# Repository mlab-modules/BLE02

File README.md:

# BLE02 - Dual-Mode Bluetooth HCI Controller

BLE02 is a dual-mode Bluetooth Low Energy controller module based on the CC2564C HCI compatible chipset.  
The module provides UART (HCI) and PCM/I²S digital audio interface and is designed as a compact MLAB building block for integration with external MCU/MPU systems.

The RF section, clocks and power conditioning are implemented on-board. The host processor should handle the Bluetooth stack via HCI transport.

## Key Features

- Dual-mode Bluetooth controller (BR/EDR + LE, Bluetooth 5.1 compliant)
- HCI transport over UART (up to 4 Mbit/s)
- PCM / I²S digital audio interface
- Class 1 transmitter capability (up to +12 dBm)
- Integrated LDO regulator from 3.3V power source
- 26 MHz main crystal oscillator
- 32.768 kHz low-power clock oscillator
- 1.8 V I/O domain (level shifted to 3.3 V on module connectors)
- Single-ended 50 Ω RF interface on MCX connector

The module uses the chip in HCI mode. All higher Bluetooth layers must run on the host MCU.

## Electrical Parameters

### Supply

- **VCC (module input):** 3.3 V nominal
- On-board regulation:
  - CC2564C powered directly from power input
  - I/O domain: 1.8 V (generated internally, exposed as VDD_1V8)
- Typical consumption:
  - TX (GFSK, max power): ~100 mA
  - LE advertising: 200 µA average
  - Shutdown: less than 10 µA

## UART Interface (HCI)

- Transport: H4 (UART)
- Baud rate: 38.4 kbit/s to 4 Mbit/s
- Hardware flow control required (RTS/CTS)

The controller signals boot completion by asserting RTS low after reset.

## Audio Interface (PCM / I²S)

- PCM master or slave mode
- Up to 4.096 MHz bit clock
- Suitable for HFP, A2DP and other audio profiles

Note: Assisted modes (WBS, A2DP assist) cannot be used simultaneously with LE mode.

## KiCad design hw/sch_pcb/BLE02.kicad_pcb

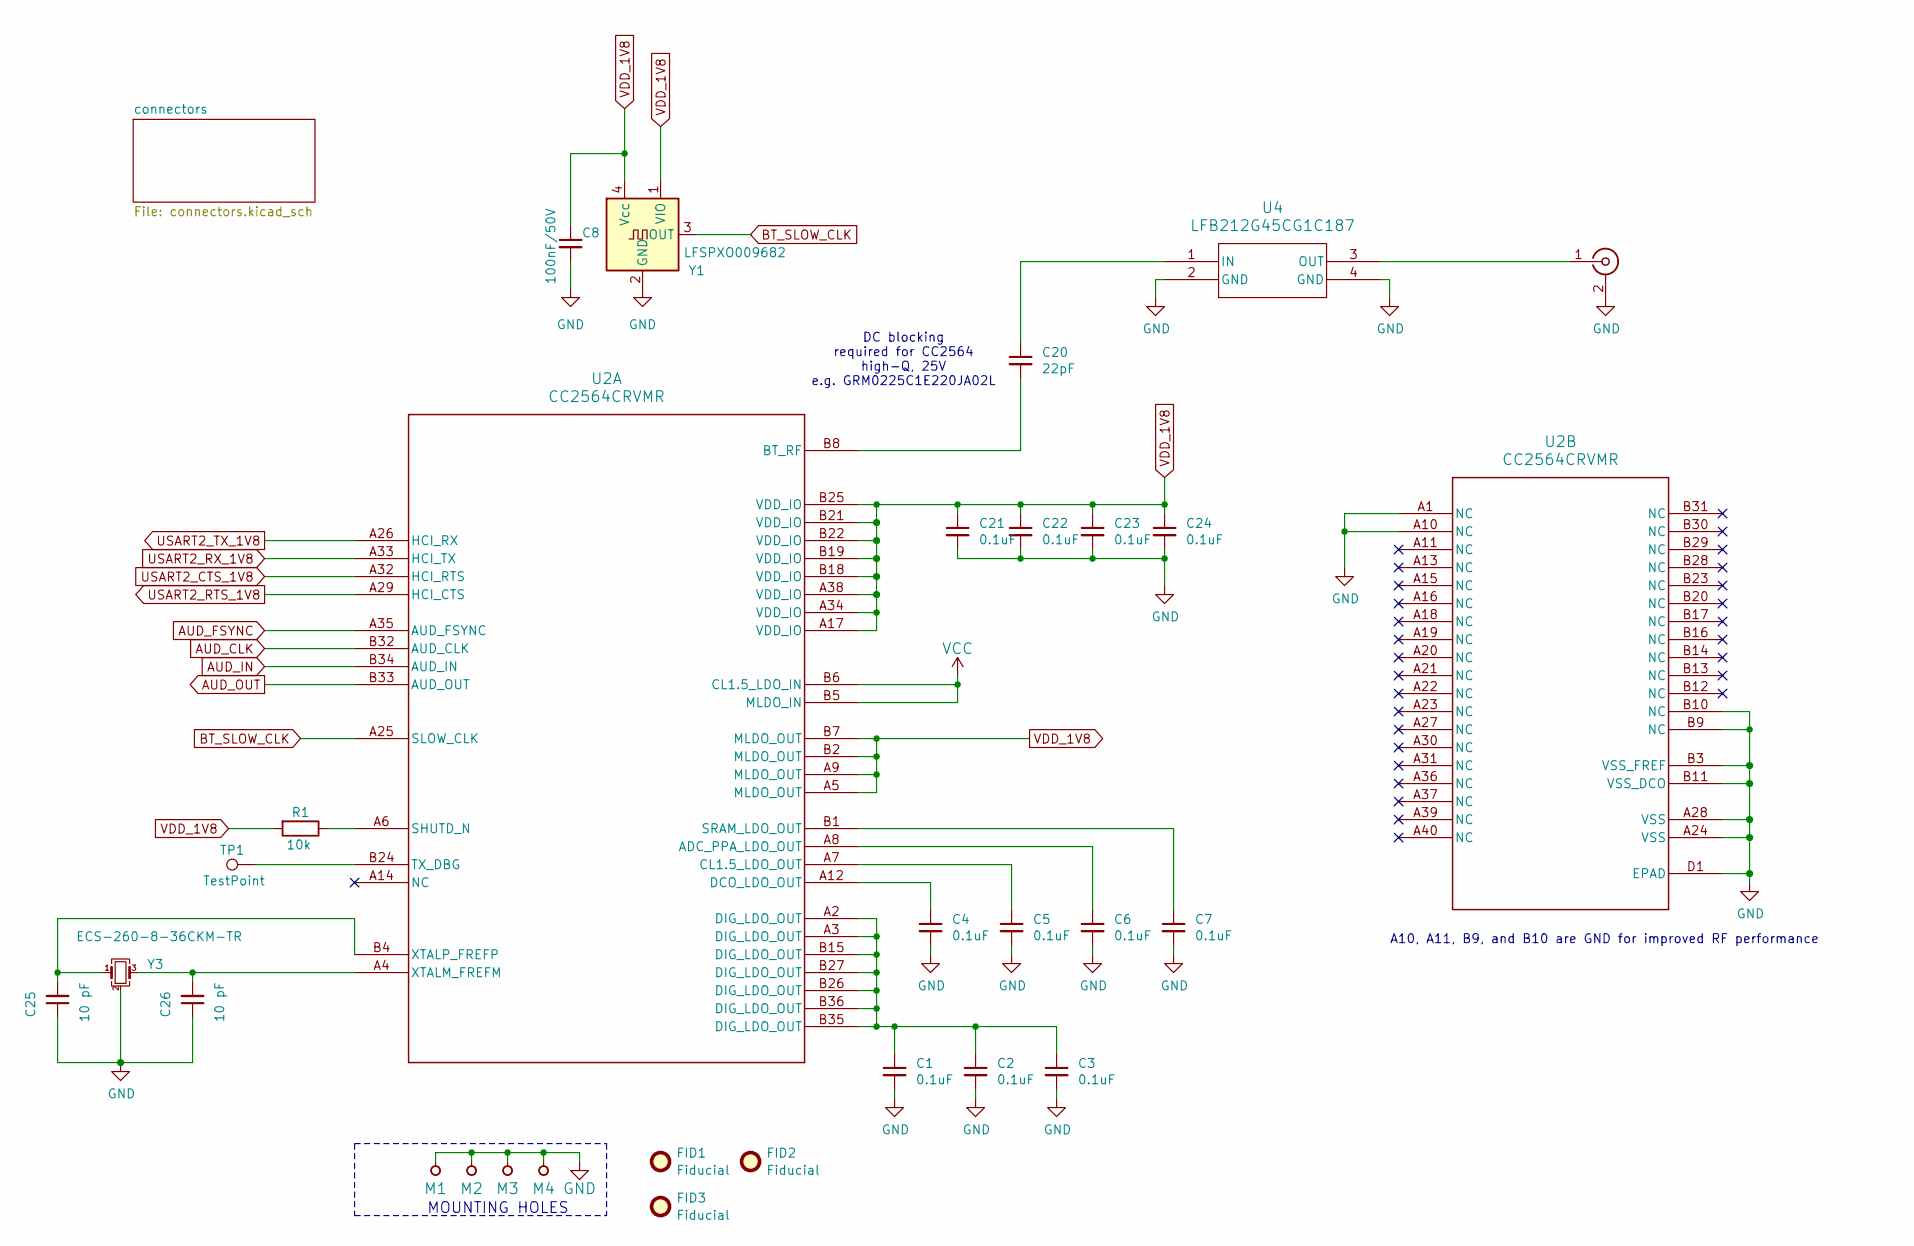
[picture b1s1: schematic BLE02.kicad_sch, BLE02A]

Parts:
C1, C2, C3, C4, C5, C6, C7, C21, C22, C23, C24: 0.1uF; C_0603_1608Metric
C8: 100nF/50V; C_0603_1608Metric
C20: 22pF; C_0603_1608Metric
C25, C26: 10 pF; C_0603_1608Metric
FID1, FID2, FID3: Fiducial; Fiducial_1mm_Mask2mm
J1: Conn_Coaxial; MCX
M1, M2, M3, M4: HOLE; MountingHole_3mm
R1: 10k; R_0603_1608Metric
TP1: TestPoint; TestPoint_Pad_D1.0mm
U2: CC2564CRVMR; RVM0076A
U4: LFB212G45CG1C187; Murata_C187
Y1: LFSPXO009682; Oscillator_SMD_SeikoEpson_SG210-4Pin_2.5x2.0mm
Y3: ECS-260-8-36CKM-TR; Crystal_SMD_2520-4Pin_2.5x2.0mm

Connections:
AUD_CLK: U2.B32 (AUD_CLK); also elsewhere on the board
AUD_FSYNC: U2.A35 (AUD_FSYNC); also elsewhere on the board
AUD_IN: U2.B34 (AUD_IN); also elsewhere on the board
AUD_OUT: U2.B33 (AUD_OUT); also elsewhere on the board
BT_SLOW_CLK: U2.A25 (SLOW_CLK), Y1.3 (OUT)
GND: C1.2, C2.2, C3.2, C4.2, C5.2, C6.2, C7.2, C8.2, C21.2, C22.2, C23.2, C24.2, C25.1, C26.1, J1.2 (Ext), M1.1, M2.1, M3.1, M4.1, U2.A1 (NC), U2.A10 (NC), U2.A24 (VSS), U2.A28 (VSS), U2.B3 (VSS_FREF), U2.B9 (NC), U2.B10 (NC), U2.B11 (VSS_DCO), U2.D1 (EPAD), U4.2 (GND), U4.4 (GND), Y1.2 (GND), Y3.2 (G), Y3.4 (G); also elsewhere on the board
unnamed: C1.1, C2.1, C3.1, U2.A2 (DIG_LDO_OUT), U2.A3 (DIG_LDO_OUT), U2.B15 (DIG_LDO_OUT), U2.B26 (DIG_LDO_OUT), U2.B27 (DIG_LDO_OUT), U2.B35 (DIG_LDO_OUT), U2.B36 (DIG_LDO_OUT)
unnamed: J1.1 (In), U4.3 (OUT)
unnamed: C6.1, U2.A8 (ADC_PPA_LDO_OUT)
unnamed: C20.2, U2.B8 (BT_RF)
unnamed: C5.1, U2.A7 (CL1.5_LDO_OUT)
unnamed: C4.1, U2.A12 (DCO_LDO_OUT)
unnamed: R1.1, U2.A6 (SHUTD_N)
unnamed: C7.1, U2.B1 (SRAM_LDO_OUT)
unnamed: TP1.1, U2.B24 (TX_DBG)
unnamed: C26.2, U2.A4 (XTALM_FREFM), Y3.3
unnamed: C25.2, U2.B4 (XTALP_FREFP), Y3.1
unnamed: C20.1, U4.1 (IN)
USART2_CTS_1V8: U2.A32 (HCI_RTS); also elsewhere on the board
USART2_RTS_1V8: U2.A29 (HCI_CTS); also elsewhere on the board
USART2_RX_1V8: U2.A33 (HCI_TX); also elsewhere on the board
USART2_TX_1V8: U2.A26 (HCI_RX); also elsewhere on the board
VCC: U2.B5 (MLDO_IN), U2.B6 (CL1.5_LDO_IN); also elsewhere on the board
VDD_1V8: C8.1, C21.1, C22.1, C23.1, C24.1, R1.2, U2.A5 (MLDO_OUT), U2.A9 (MLDO_OUT), U2.A17 (VDD_IO), U2.A34 (VDD_IO), U2.A38 (VDD_IO), U2.B2 (MLDO_OUT), U2.B7 (MLDO_OUT), U2.B18 (VDD_IO), U2.B19 (VDD_IO), U2.B21 (VDD_IO), U2.B22 (VDD_IO), U2.B25 (VDD_IO), Y1.1 (VIO), Y1.4 (Vcc); also elsewhere on the board

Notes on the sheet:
DC blocking required for CC2564 high-Q, 25V e.g. GRM0225C1E220JA02L
MOUNTING HOLES
A10, A11, B9, and B10 are GND for improved RF performance

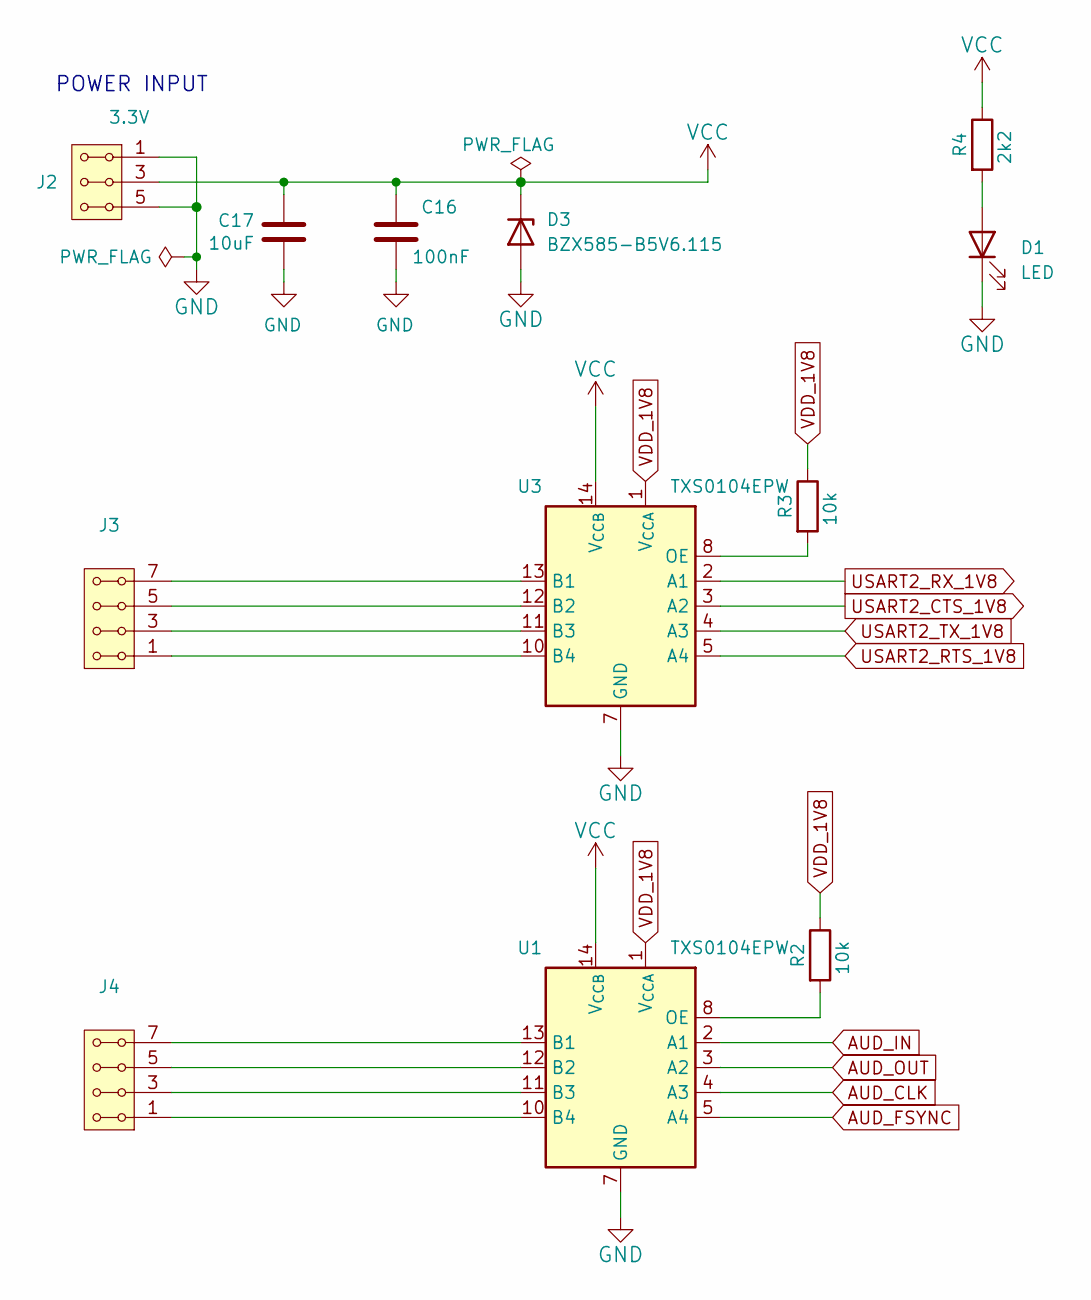
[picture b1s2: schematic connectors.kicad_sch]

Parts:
C16: 100nF; C_0603_1608Metric
C17: 10uF; C_0805_2012Metric
D1: LED; LED_1206_mill
D3: BZX585-B5V6.115; D_SOD-523
J2: 3.3V; Straight_2x03
J3, J4: JUMP_5X2; Straight_2x04
R2, R3: 10k; R_0603_1608Metric
R4: 2k2; R_0603_1608Metric
U1, U3: TXS0104EPW; TSSOP-14_4.4x5mm_P0.65mm

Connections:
AUD_CLK: U1.4 (A3); also elsewhere on the board
AUD_FSYNC: U1.5 (A4); also elsewhere on the board
AUD_IN: U1.2 (A1); also elsewhere on the board
AUD_OUT: U1.3 (A2); also elsewhere on the board
GND: C16.2, C17.2, D1.1 (K), D3.2 (A), J2.1, J2.2, J2.5, J2.6, U1.7 (GND), U3.7 (GND); also elsewhere on the board
unnamed: D1.2 (A), R4.2
unnamed: J4.7, J4.8, U1.13 (B1)
unnamed: J4.5, J4.6, U1.12 (B2)
unnamed: J4.3, J4.4, U1.11 (B3)
unnamed: J4.1, J4.2, U1.10 (B4)
unnamed: R2.2, U1.8 (OE)
unnamed: J3.7, J3.8, U3.13 (B1)
unnamed: J3.5, J3.6, U3.12 (B2)
unnamed: J3.3, J3.4, U3.11 (B3)
unnamed: J3.1, J3.2, U3.10 (B4)
unnamed: R3.2, U3.8 (OE)
USART2_CTS_1V8: U3.3 (A2); also elsewhere on the board
USART2_RTS_1V8: U3.5 (A4); also elsewhere on the board
USART2_RX_1V8: U3.2 (A1); also elsewhere on the board
USART2_TX_1V8: U3.4 (A3); also elsewhere on the board
VCC: C16.1, C17.1, D3.1 (K), J2.3, J2.4, R4.1, U1.14 (V_{CCB}), U3.14 (V_{CCB}); also elsewhere on the board
VDD_1V8: R2.1, R3.1, U1.1 (V_{CCA}), U3.1 (V_{CCA}); also elsewhere on the board

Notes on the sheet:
POWER INPUT

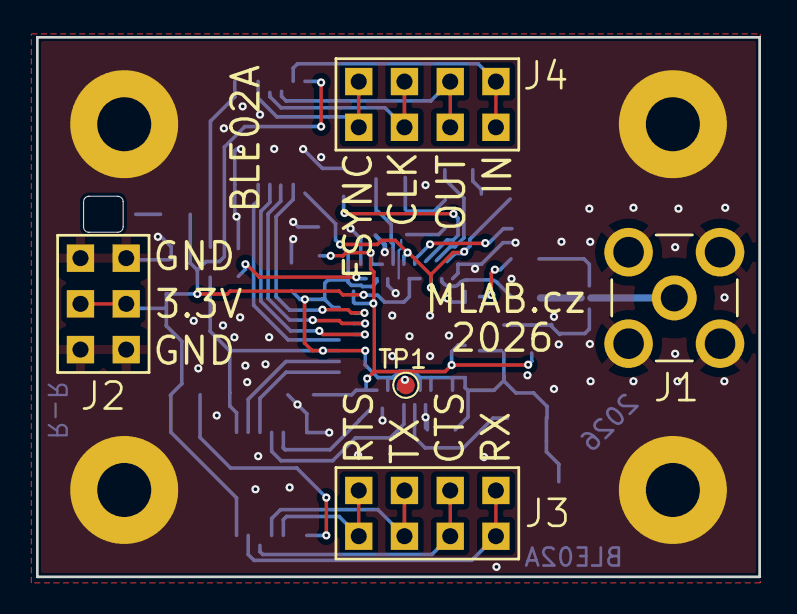
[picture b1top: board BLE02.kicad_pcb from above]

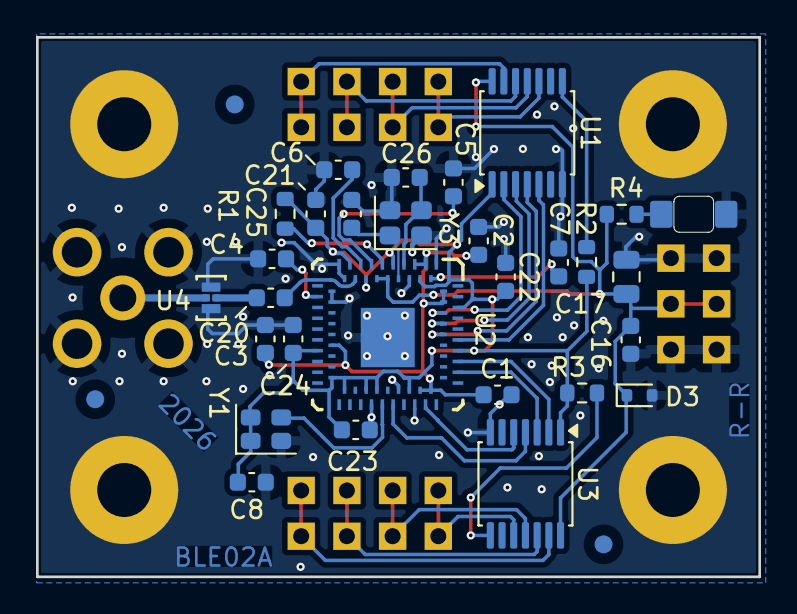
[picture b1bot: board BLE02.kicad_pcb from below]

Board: 2 copper layers, 40.1 x 30.0 mm, 41 parts (32 on the bottom side), 35 nets.

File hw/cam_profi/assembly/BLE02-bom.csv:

Component,Description,Part,References,Value,Footprint,Quantity Per PCB,Datasheet,ust_id
1,,C-Device,C25C26,10 pF,C_0603_1608Metric,2,~,
2,,C-Device,C20,22pF,C_0603_1608Metric,1,~,
3,Unpolarized capacitor,C,C16,100nF,C_0603_1608Metric,1,~,5c70984712875079b91f8b4c
4,,C-Device,C21C22C23C24,0.1uF,C_0603_1608Metric,4,~,
5,Unpolarized capacitor,C,C17,10uF,C_0805_2012Metric,1,~,5c70984812875079b91f8bbe
6,Zener diode,D_Zener,D3,"BZV55C-6,2V",D_MiniMELF,1,~,604b0326128750769e5b0f93
7,,DEA202450BT-1213C1,FL1,DEA202450BT-1213C1,DEA202450BT-1213C1,1,,
8,"2x03 2.54 mm pitch header, 2 pins next to each other are connected",HEADER_2x03_PARALLEL,J2,3.3-5V,Straight_2x03,1,,
9,"coaxial connector (BNC, SMA, SMB, SMC, Cinch/RCA, LEMO, ...)",Conn_Coaxial,J1,Conn_Coaxial,MCX,1,~,
10,"2x04 2.54 mm pitch header, 2 pins next to each other are connected",HEADER_2x04_PARALLEL,J3J4,JUMP_5X2,Straight_2x04,2,,
11,,R-Device,R18,0,R_0603_1608Metric,1,~,
12,,CC2564CRVMR,U2,CC2564CRVMR,RVM0076A,1,https://www.ti.com/lit/gpn/cc2564c,
13,"Bidirectional  level-shifting voltage translator, TSSOP-14",TXS0104EPW,U1U3,TXS0104EPW,TSSOP-14_4.4x5mm_P0.65mm,2,www.ti.com/lit/ds/symlink/txs0104e.pdf,
14,,Crystal_GND24_Small-Device,Y3,ECS-260-8-36CKM-TR,XTAL_ECS-260-8-36CKM-TR,1,~,

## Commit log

2026-01-22 Update workflow files
2026-01-22 Update metadata files
2026-01-22 Commiting modified design from https://github.com/mattkelly/stm32-cc2564-board
2026-01-22 Update actions products
2026-02-08 Connectors placement on the board
2026-02-08 Update project workflows.
2026-02-08 Fix footprint of pin-headers.
2026-02-08 Add text for connectors
2026-02-08 Connect B10 to gnd
2026-02-10 Improve layout.
2026-02-14 Cleanup layout. Fix obsolete part types.
2026-02-14 Cleanup and update documentation.
2026-02-15 Automatic update of KiCAD outputs
2026-02-15 Cleanup layout and silkscreen.
2026-02-20 Update UST_IDs.
